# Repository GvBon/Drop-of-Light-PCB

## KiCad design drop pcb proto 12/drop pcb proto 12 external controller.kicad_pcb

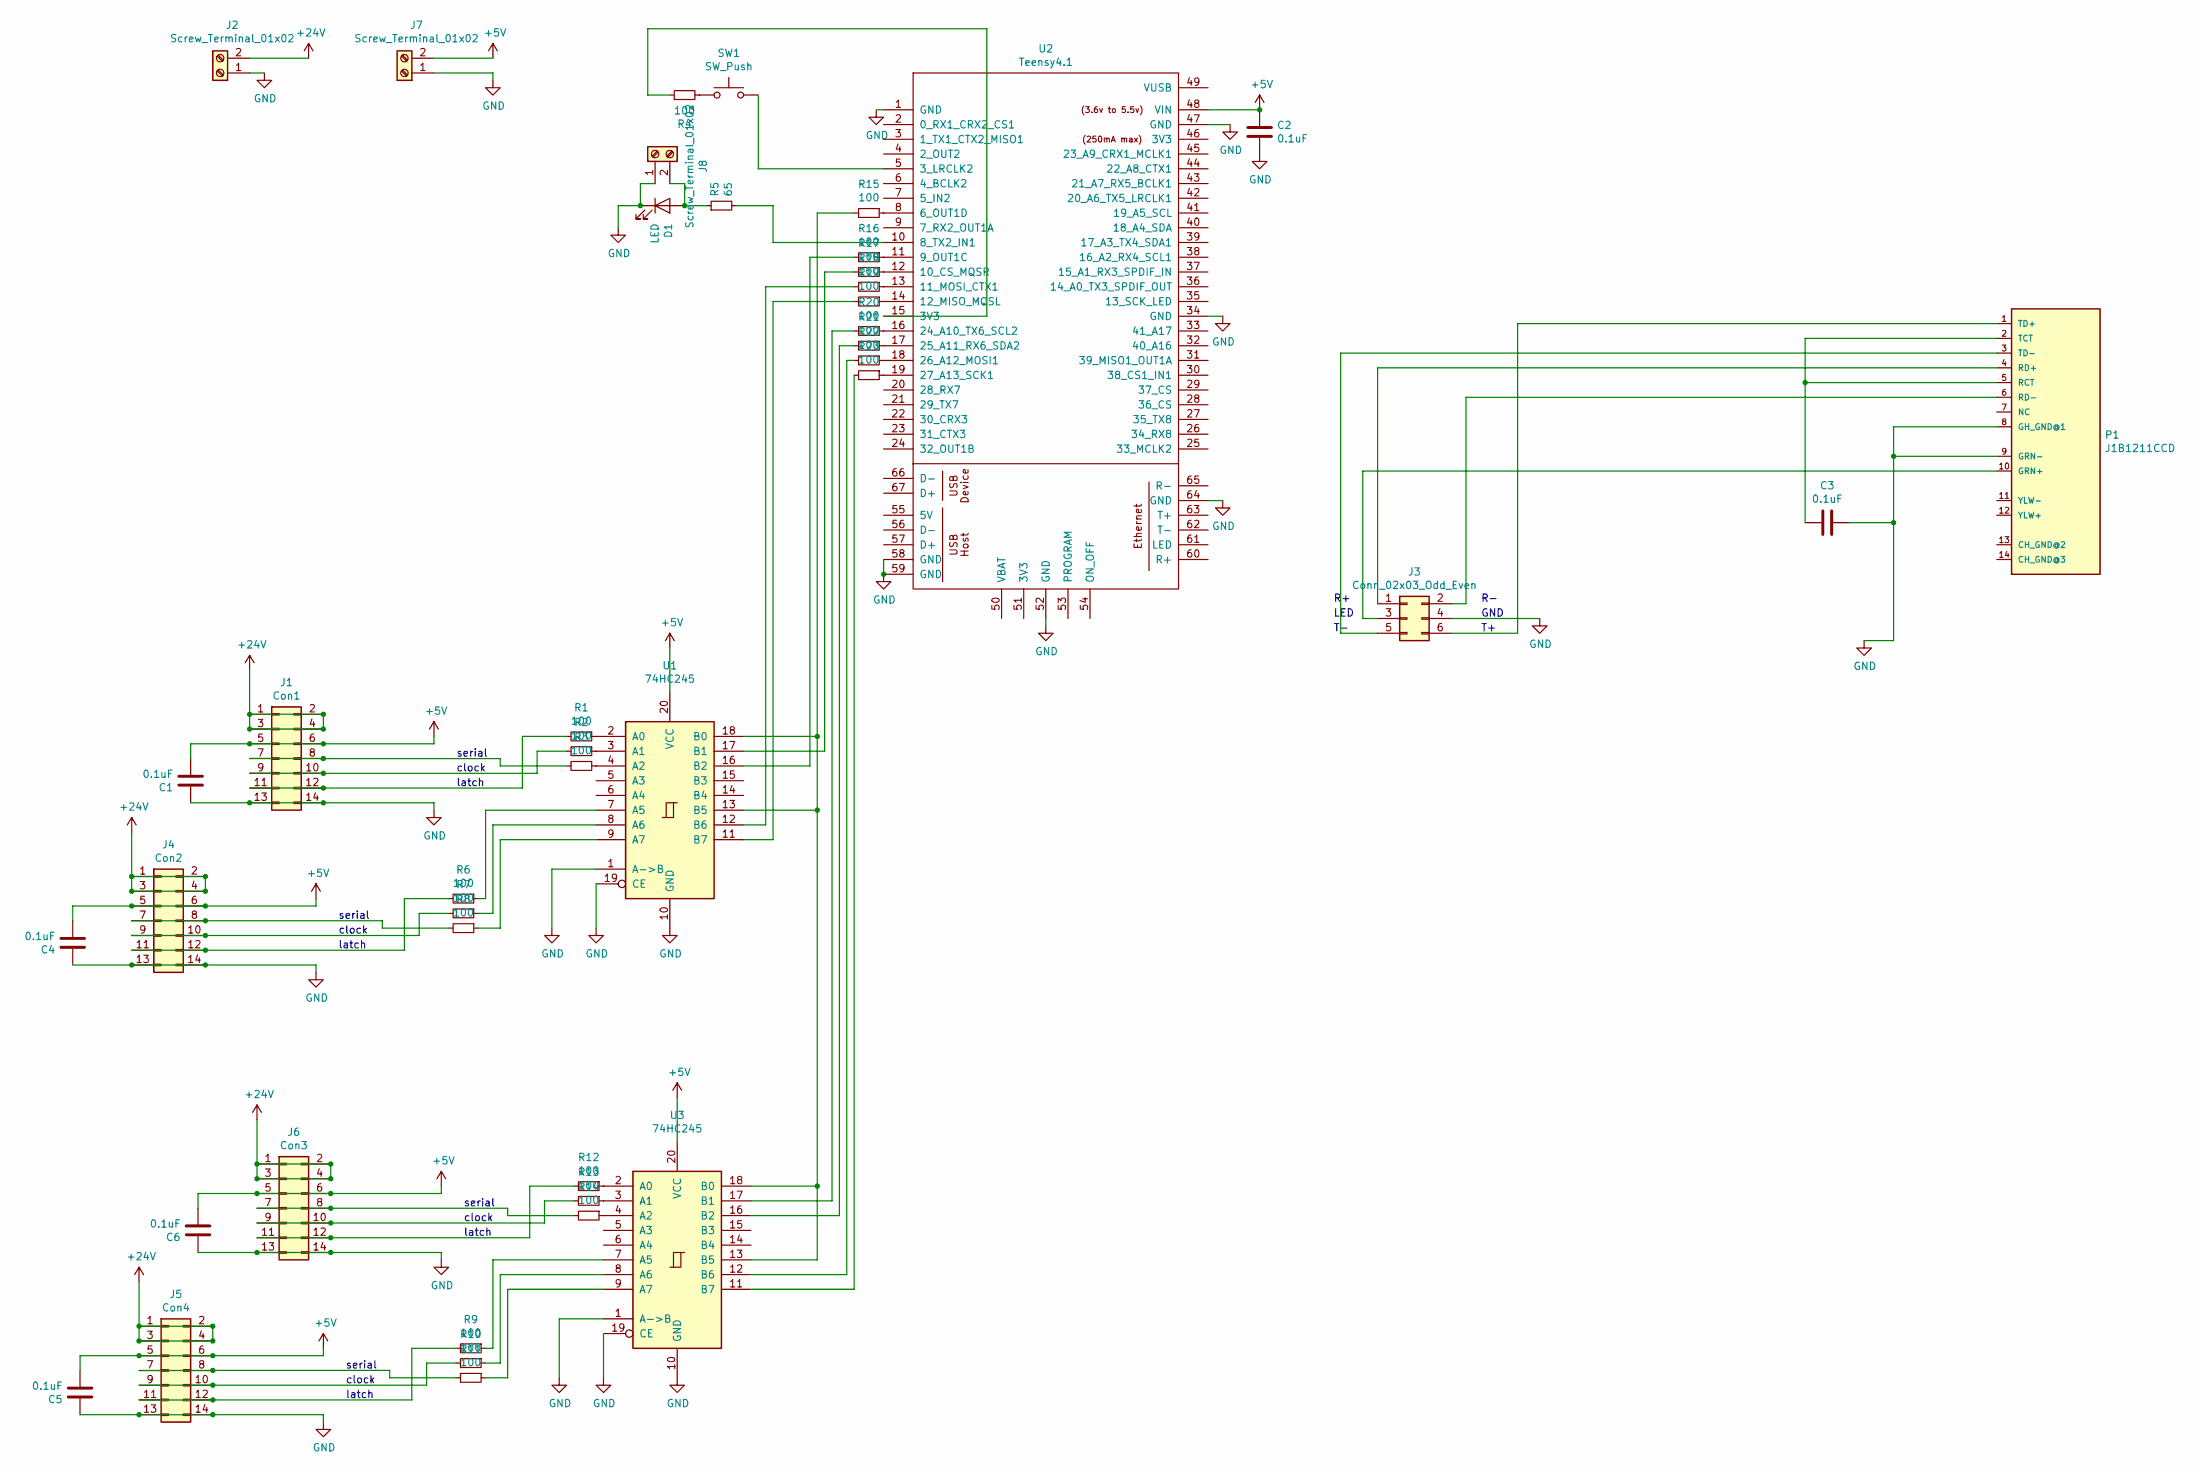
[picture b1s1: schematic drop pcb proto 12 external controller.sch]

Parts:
C1, C4, C5, C6: 0.1uF; C_Disc_D4.7mm_W2.5mm_P5.00mm
C2, C3: 0.1uF; C_Disc_D5.0mm_W2.5mm_P5.00mm
D1: LED; LED_D5.0mm
J1: Con1; PinSocket_2x07_P2.54mm_Vertical
J2, J7, J8: Screw_Terminal_01x02; TerminalBlock_MetzConnect_Type073_RT02602HBLU_1x02_P5.08mm_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
J3: Conn_02x03_Odd_Even; PinHeader_2x03_P2.00mm_Vertical
J4: Con2; PinSocket_2x07_P2.54mm_Vertical
J5: Con4; PinSocket_2x07_P2.54mm_Vertical
J6: Con3; PinSocket_2x07_P2.54mm_Vertical
P1: J1B1211CCD
R1, R2, R3, R4, R6, R7, R8, R9, R10, R11, R12, R13, R14, R15, R16, R17, R18, R19, R20, R21, R22, R23: 100; R_Axial_DIN0207_L6.3mm_D2.5mm_P10.16mm_Horizontal
R5: 65; R_Axial_DIN0207_L6.3mm_D2.5mm_P10.16mm_Horizontal
SW1: SW_Push; SW_PUSH_6mm
U1, U3: 74HC245; DIP-20_W7.62mm_LongPads
U2: Teensy4.1; Teensy41

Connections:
+5V: C1.2, C2.1, C4.2, C5.2, C6.2, J1.5, J1.6, J4.5, J4.6, J5.5, J5.6, J6.5, J6.6, J7.2, U1.20 (VCC), U2.48 (VIN), U3.20 (VCC)
+24V: J1.1, J1.2, J1.3, J1.4, J2.2, J4.1, J4.2, J4.3, J4.4, J5.1, J5.2, J5.3, J5.4, J6.1, J6.2, J6.3, J6.4
GND: C1.1, C2.2, C3.2, C4.1, C5.1, C6.1, D1.1 (K), J1.13, J1.14, J2.1, J3.4, J4.13, J4.14, J5.13, J5.14, J6.13, J6.14, J7.1, J8.1, P1.8 (GH_GND@1), P1.9 (GRN-), U1.1 (A->B), U1.10 (GND), U1.19 (CE), U2.1 (GND), U2.34 (GND), U2.47 (GND), U2.52 (GND), U2.58 (GND), U2.59 (GND), U2.64 (GND), U3.1 (A->B), U3.10 (GND), U3.19 (CE)
unnamed: C3.1, P1.2 (TCT), P1.5 (RCT)
unnamed: D1.2 (A), J8.2, R5.1
unnamed: J1.7, J1.8, R3.2
unnamed: J1.9, J1.10, R2.2
unnamed: J1.11, J1.12, R1.2
unnamed: J3.1, P1.4 (RD+)
unnamed: J3.2, P1.6 (RD-)
unnamed: J3.3, P1.10 (GRN+)
unnamed: J3.5, P1.3 (TD-)
unnamed: J3.6, P1.1 (TD+)
unnamed: J4.7, J4.8, R8.2
unnamed: J4.9, J4.10, R7.2
unnamed: J4.11, J4.12, R6.2
unnamed: J5.7, J5.8, R11.2
unnamed: J5.9, J5.10, R10.2
unnamed: J5.11, J5.12, R9.2
unnamed: J6.7, J6.8, R14.2
unnamed: J6.9, J6.10, R13.2
unnamed: J6.11, J6.12, R12.2
unnamed: R1.1, U1.2 (A0)
unnamed: R2.1, U1.3 (A1)
unnamed: R3.1, U1.4 (A2)
unnamed: R4.1, U2.15 (3V3)
unnamed: R4.2, SW1.1
unnamed: R5.2, U2.10 (8_TX2_IN1)
unnamed: R6.1, U1.7 (A5)
unnamed: R7.1, U1.8 (A6)
unnamed: R8.1, U1.9 (A7)
unnamed: R9.1, U3.7 (A5)
unnamed: R10.1, U3.8 (A6)
unnamed: R11.1, U3.9 (A7)
unnamed: R12.1, U3.2 (A0)
unnamed: R13.1, U3.3 (A1)
unnamed: R14.1, U3.4 (A2)
unnamed: R15.1, U2.8 (6_OUT1D)
unnamed: R15.2, U1.13 (B5), U1.18 (B0), U3.13 (B5), U3.18 (B0)
unnamed: R16.1, U2.11 (9_OUT1C)
unnamed: R16.2, U1.16 (B2)
unnamed: R17.1, U2.12 (10_CS_MQSR)
unnamed: R17.2, U1.17 (B1)
unnamed: R18.1, U2.13 (11_MOSI_CTX1)
unnamed: R18.2, U1.12 (B6)
unnamed: R19.1, U2.14 (12_MISO_MQSL)
unnamed: R19.2, U1.11 (B7)
unnamed: R20.1, U2.16 (24_A10_TX6_SCL2)
unnamed: R20.2, U3.17 (B1)
unnamed: R21.1, U2.17 (25_A11_RX6_SDA2)
unnamed: R21.2, U3.16 (B2)
unnamed: R22.1, U2.18 (26_A12_MOSI1)
unnamed: R22.2, U3.12 (B6)
unnamed: R23.1, U2.19 (27_A13_SCK1)
unnamed: R23.2, U3.11 (B7)
unnamed: SW1.2, U2.5 (3_LRCLK2)

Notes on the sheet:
latch
clock
serial
LED
GND

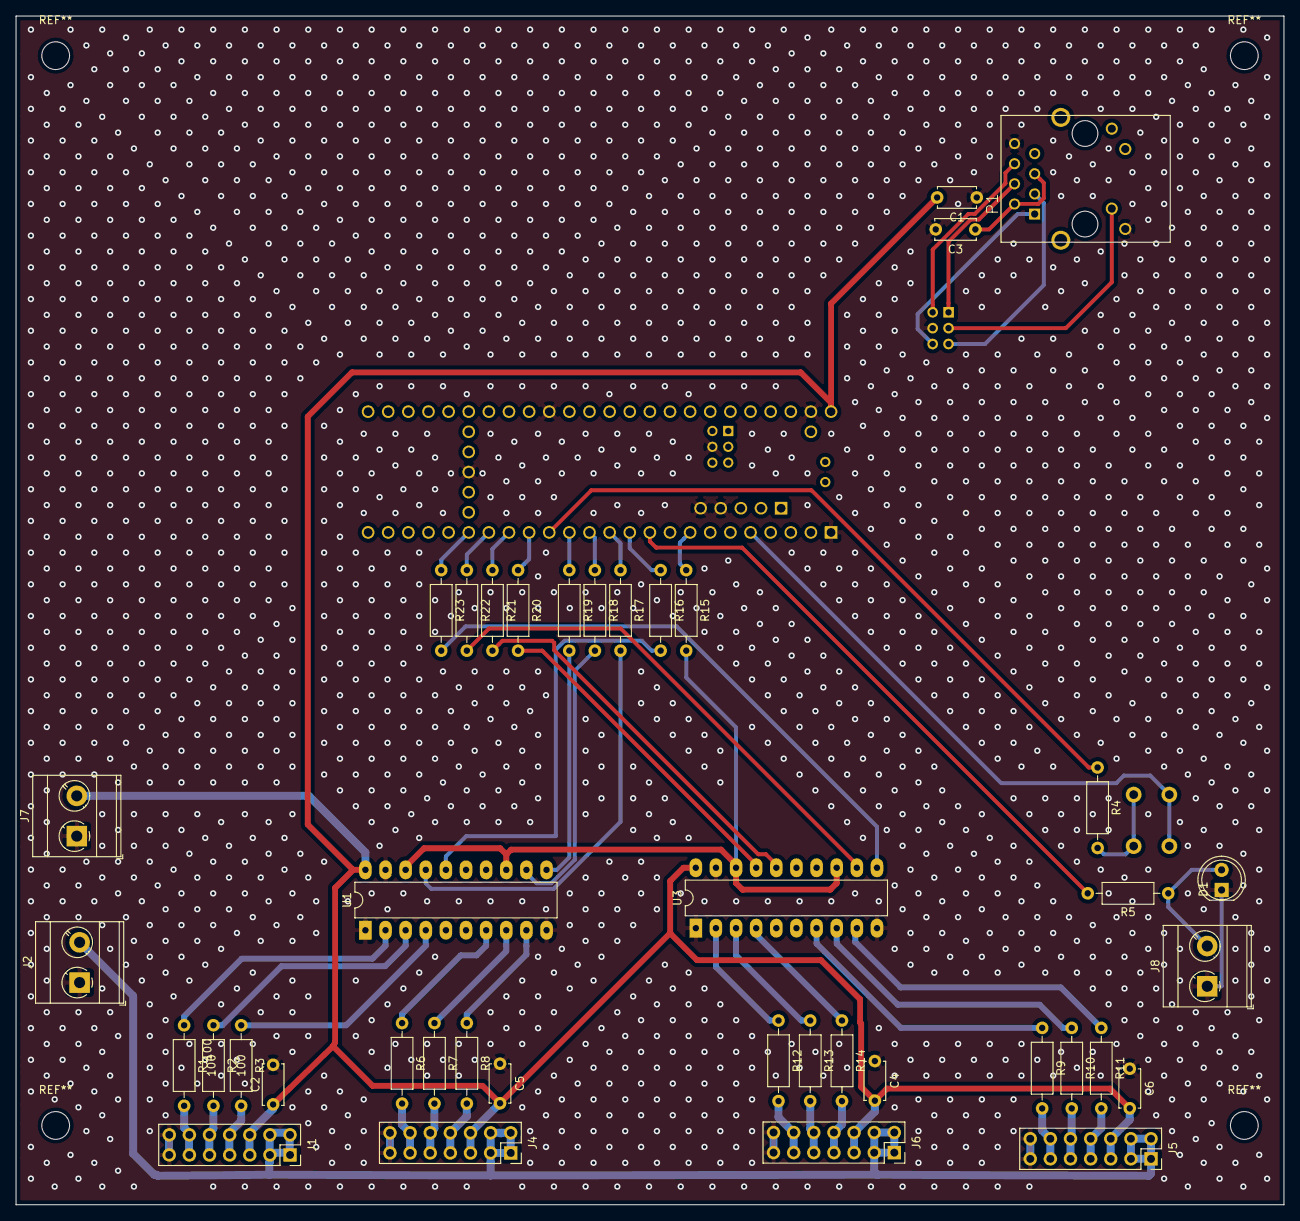
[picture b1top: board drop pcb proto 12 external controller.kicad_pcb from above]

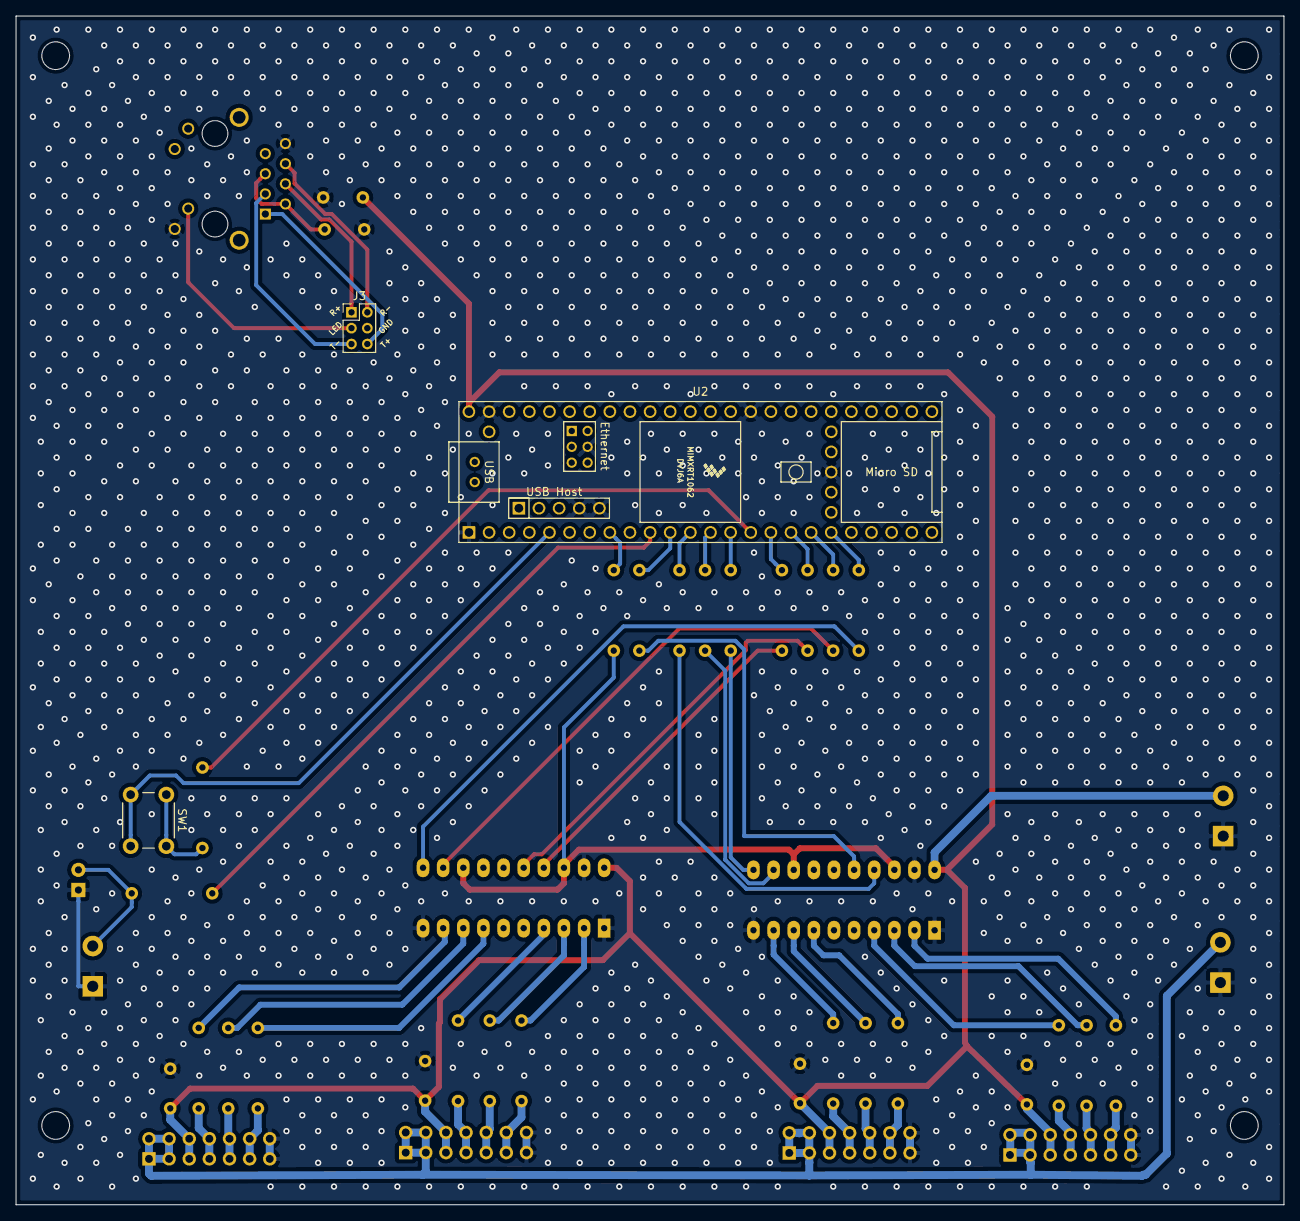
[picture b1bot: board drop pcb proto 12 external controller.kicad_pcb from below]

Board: 2 copper layers, 160.0 x 150.0 mm, 43 parts (3 on the bottom side), 56 nets.

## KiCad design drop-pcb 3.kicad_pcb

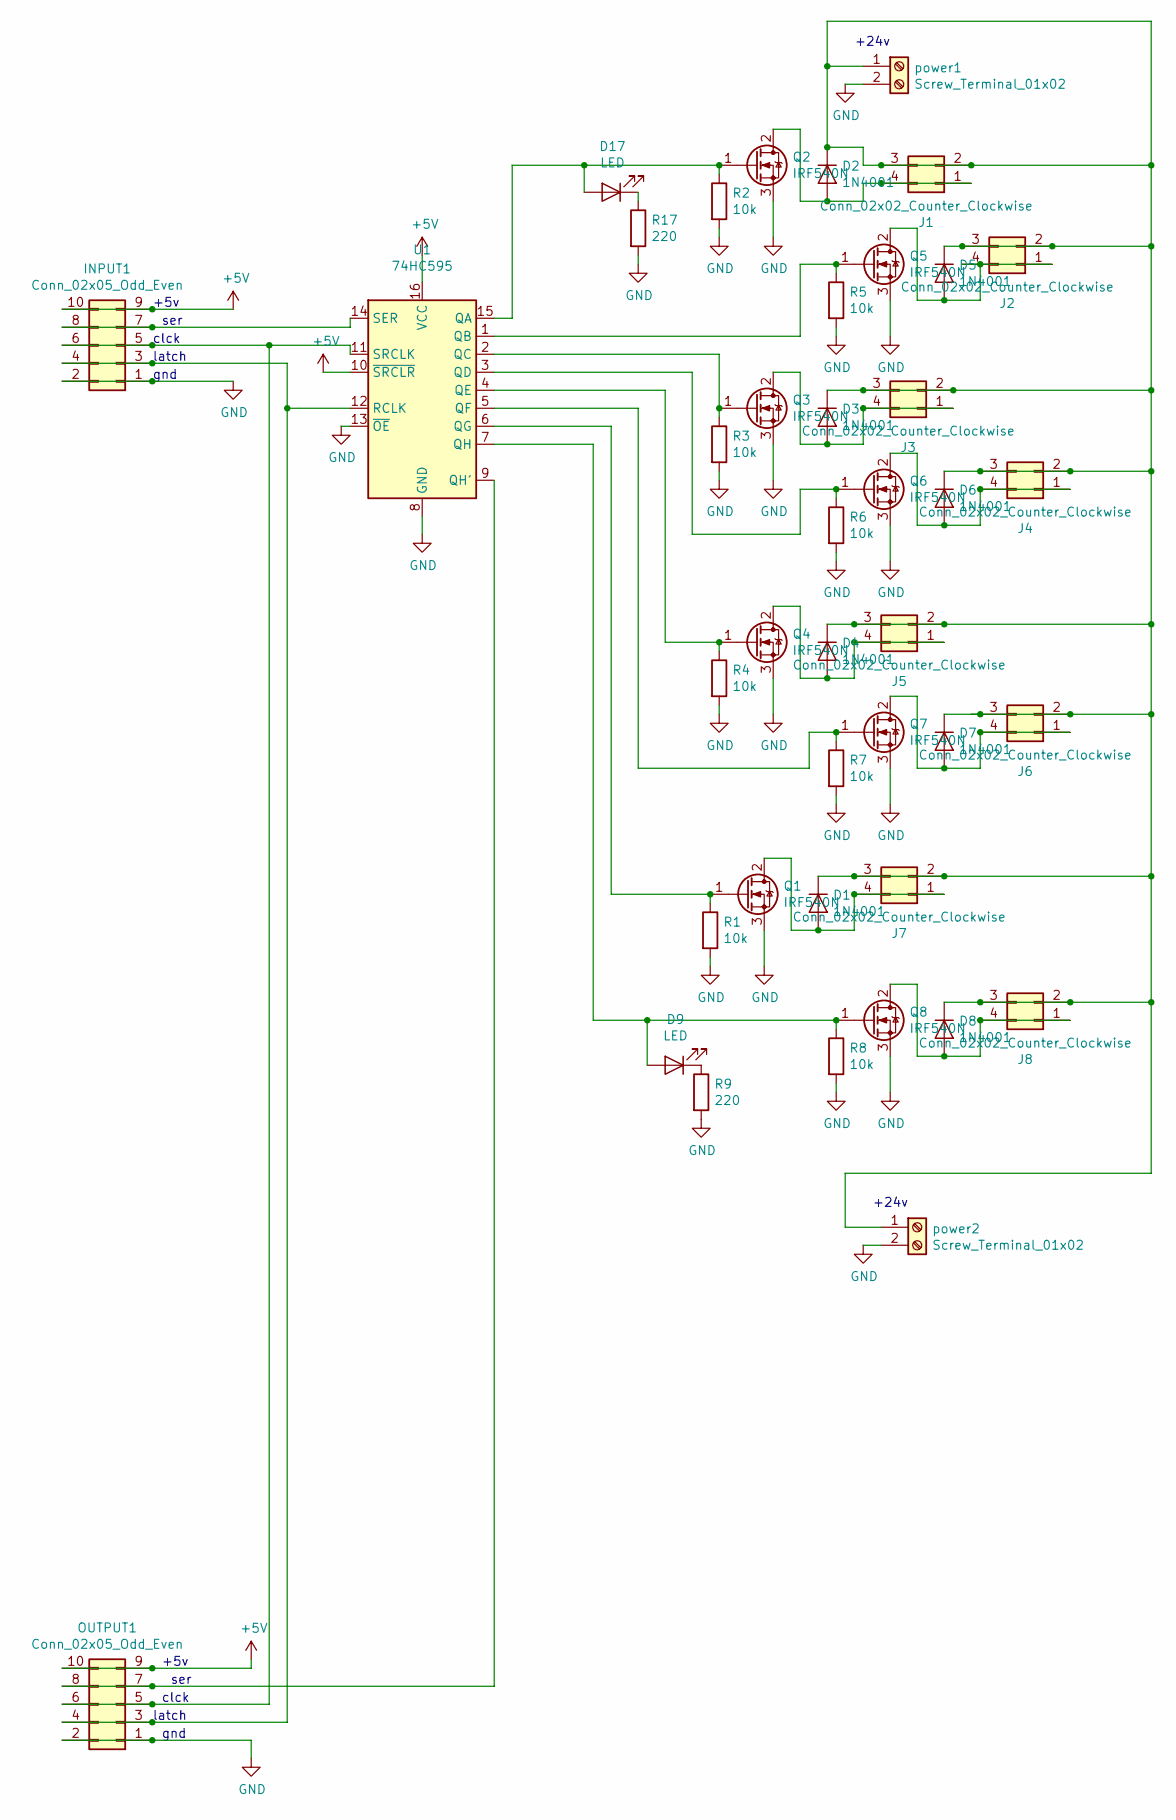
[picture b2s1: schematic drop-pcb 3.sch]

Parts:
D1, D2, D3, D4, D5, D6, D7, D8: 1N4001; D_DO-41_SOD81_P10.16mm_Horizontal
D9, D17: LED; LED_D3.0mm
INPUT1: Conn_02x05_Odd_Even; PinSocket_2x05_P2.54mm_Vertical
J1, J2, J3, J4, J5, J6, J7, J8: Conn_02x02_Counter_Clockwise; SOLGijs
OUTPUT1: Conn_02x05_Odd_Even; PinSocket_2x05_P2.54mm_Vertical
Q1, Q2, Q3, Q4, Q5, Q6, Q7, Q8: IRF540N; TO-220-3_Vertical
R1, R2, R3, R4, R5, R6, R7, R8: 10k; R_Axial_DIN0309_L9.0mm_D3.2mm_P12.70mm_Horizontal
R9, R17: 220; R_Axial_DIN0309_L9.0mm_D3.2mm_P12.70mm_Horizontal
U1: 74HC595; DIP-16_W7.62mm_LongPads
power1, power2: Screw_Terminal_01x02; TerminalBlock_bornier-2_P5.08mm

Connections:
+5V: INPUT1.9, INPUT1.10, OUTPUT1.9, OUTPUT1.10, U1.10 (~SRCLR), U1.16 (VCC)
GND: INPUT1.1, INPUT1.2, OUTPUT1.1, OUTPUT1.2, Q1.3 (S), Q2.3 (S), Q3.3 (S), Q4.3 (S), Q5.3 (S), Q6.3 (S), Q7.3 (S), Q8.3 (S), R1.2, R2.2, R3.2, R4.2, R5.2, R6.2, R7.2, R8.2, R9.2, R17.2, U1.8 (GND), U1.13 (~OE), power1.2, power2.2
unnamed: D1.1 (K), D2.1 (K), D3.1 (K), D4.1 (K), D5.1 (K), D6.1 (K), D7.1 (K), D8.1 (K), J1.2, J1.3, J2.2, J2.3, J3.2, J3.3, J4.2, J4.3, J5.2, J5.3, J6.2, J6.3, J7.2, J7.3, J8.2, J8.3, power1.1, power2.1
unnamed: D1.2 (A), J7.1, J7.4, Q1.2 (D)
unnamed: D2.2 (A), J1.1, J1.4, Q2.2 (D)
unnamed: D3.2 (A), J3.1, J3.4, Q3.2 (D)
unnamed: D4.2 (A), J5.1, J5.4, Q4.2 (D)
unnamed: D5.2 (A), J2.1, J2.4, Q5.2 (D)
unnamed: D6.2 (A), J4.1, J4.4, Q6.2 (D)
unnamed: D7.2 (A), J6.1, J6.4, Q7.2 (D)
unnamed: D8.2 (A), J8.1, J8.4, Q8.2 (D)
unnamed: D9.1 (K), R9.1
unnamed: D9.2 (A), Q8.1 (G), R8.1, U1.7 (QH)
unnamed: D17.1 (K), R17.1
unnamed: D17.2 (A), Q2.1 (G), R2.1, U1.15 (QA)
unnamed: INPUT1.3, INPUT1.4, OUTPUT1.3, OUTPUT1.4, U1.12 (RCLK)
unnamed: INPUT1.5, INPUT1.6, OUTPUT1.5, OUTPUT1.6, U1.11 (SRCLK)
unnamed: INPUT1.7, INPUT1.8, U1.14 (SER)
unnamed: OUTPUT1.7, OUTPUT1.8, U1.9 (QH')
unnamed: Q1.1 (G), R1.1, U1.6 (QG)
unnamed: Q3.1 (G), R3.1, U1.2 (QC)
unnamed: Q4.1 (G), R4.1, U1.4 (QE)
unnamed: Q5.1 (G), R5.1, U1.1 (QB)
unnamed: Q6.1 (G), R6.1, U1.3 (QD)
unnamed: Q7.1 (G), R7.1, U1.5 (QF)

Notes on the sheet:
+24v
ser
clck
latch
+5v
gnd

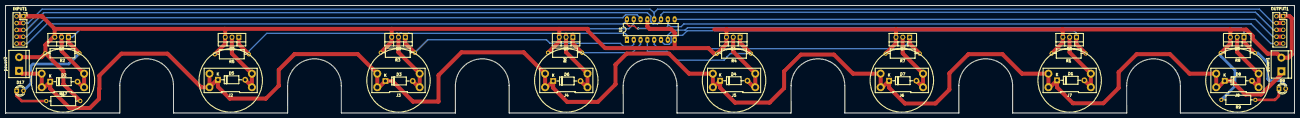
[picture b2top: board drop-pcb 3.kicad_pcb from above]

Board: 2 copper layers, 480.1 x 40.0 mm, 41 parts (0 on the bottom side), 25 nets.

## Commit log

2022-01-18 version 12, big controller board
